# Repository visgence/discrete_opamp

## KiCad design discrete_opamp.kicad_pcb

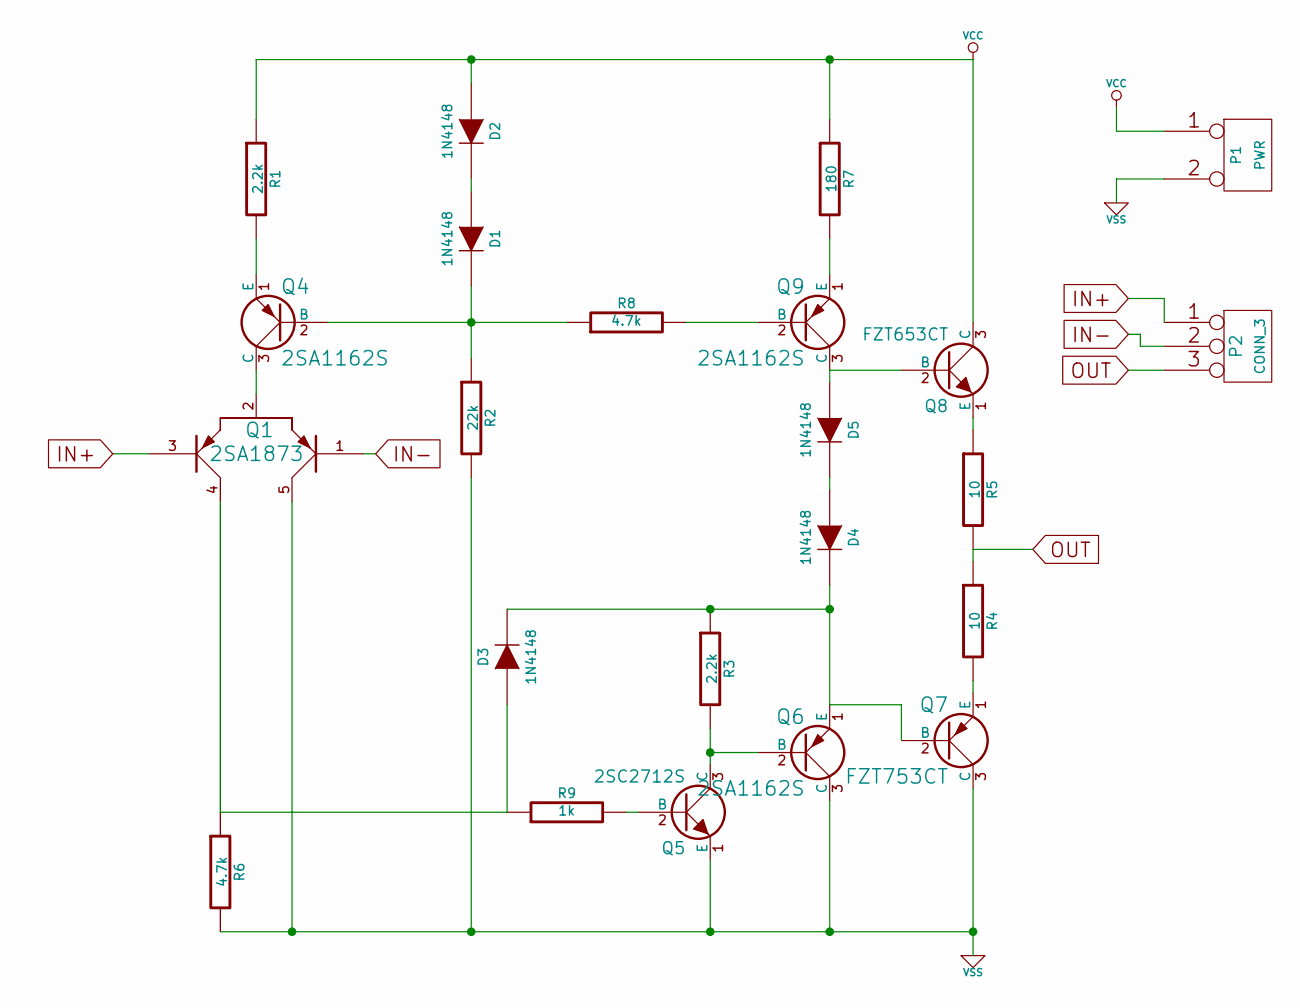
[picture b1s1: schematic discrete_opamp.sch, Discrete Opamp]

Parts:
D1, D2, D3, D4, D5: 1N4148
P1: PWR
P2: CONN_3
Q1: 2SA1873
Q4, Q6, Q9: 2SA1162S
Q5: 2SC2712S
Q7: FZT753CT
Q8: FZT653CT
R1, R3: 2.2k
R2: 22k
R4, R5: 10
R6, R8: 4.7k
R7: 180
R9: 1k

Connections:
IN+: P2.1, Q1.3
IN-: P2.2 (PM), Q1.1
unnamed: Q7.1 (E), R4.2
unnamed: D5.1 (A), Q8.2 (B), Q9.3 (C)
unnamed: Q8.1 (E), R5.1
unnamed: D4.1 (A), D5.2 (K)
unnamed: D3.1 (A), Q1.4, R6.1, R9.1
unnamed: Q5.2 (B), R9.2
unnamed: D1.1 (A), D2.2 (K)
unnamed: Q9.1 (E), R7.2
unnamed: Q9.2 (B), R8.2
unnamed: D1.2 (K), Q4.2 (B), R2.1, R8.1
unnamed: Q1.2, Q4.3 (C)
unnamed: Q4.1 (E), R1.2
unnamed: Q5.3 (C), Q6.2 (B), R3.2
unnamed: D3.2 (K), D4.2 (K), Q6.1 (E), Q7.2 (B), R3.1
OUT: P2.3, R4.1, R5.2
VCC: D2.1 (A), P1.1, Q8.3 (C), R1.1, R7.1
VSS: P1.2 (PM), Q1.5, Q5.1 (E), Q6.3 (C), Q7.3 (C), R2.2, R6.2

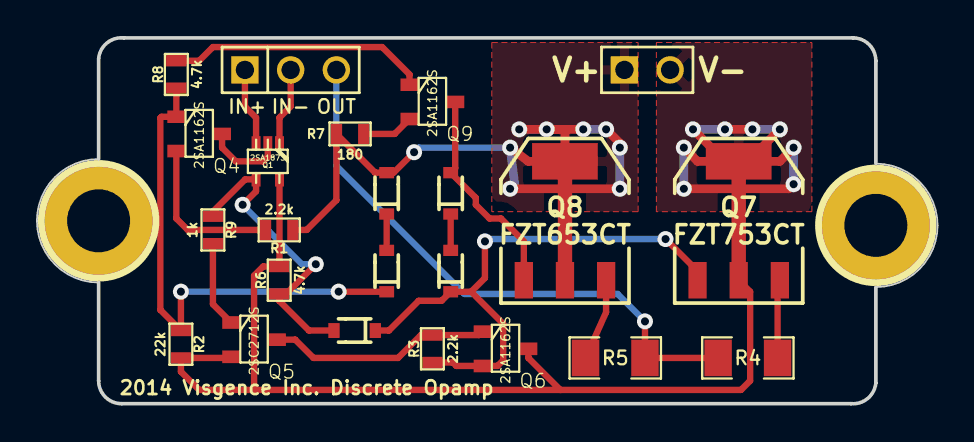
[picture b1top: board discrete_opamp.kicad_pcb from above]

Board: 2 copper layers, 50.0 x 20.3 mm, 25 parts (0 on the bottom side), 19 nets.

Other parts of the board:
h1, h2: pin; 1pin_C

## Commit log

2014-01-18 Added annotations and connections
2014-01-18 Changed path to relative
2014-01-18 Created netlist, started association
2014-01-18 Finished association
2014-01-23 Fix misspelling of descrete
2014-01-29 Started PCB board
2014-02-05 Fixed border, added silkscreen text
2014-02-05 Just did some final checks
2014-02-05 Created gerber files
